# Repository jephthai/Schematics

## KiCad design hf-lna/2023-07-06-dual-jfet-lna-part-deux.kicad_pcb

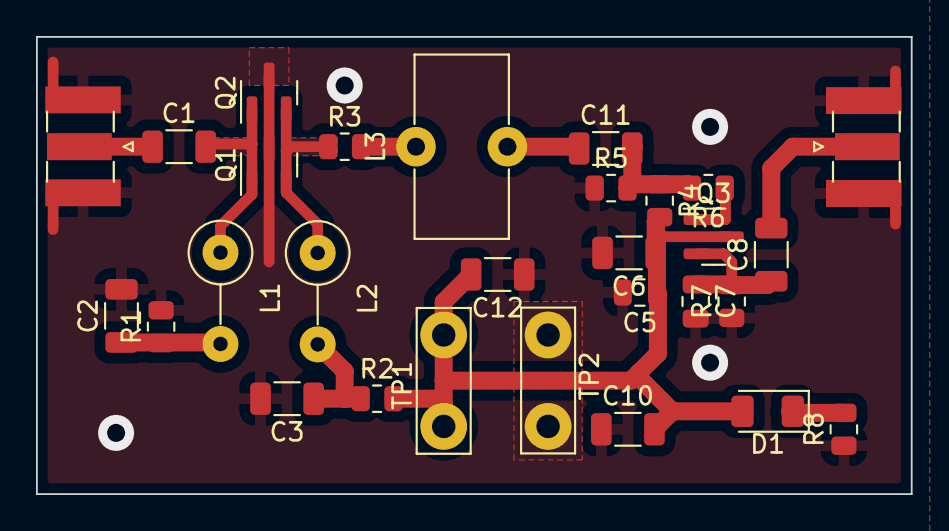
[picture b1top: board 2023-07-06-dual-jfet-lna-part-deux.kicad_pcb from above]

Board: 2 copper layers, 48.6 x 25.4 mm, 29 parts (0 on the bottom side), 14 nets.

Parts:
C1, C2, C3, C6, C8, C11, C12: 100n; C_1206_3216Metric
C5: 10n; C_0805_2012Metric
C7: 20p; C_0805_2012Metric
C10: 10u; C_1206_3216Metric
D1: LED; LED_1206_3216Metric
J1: RFIN; SMA-edge-mount
J2: RFOUT; SMA-edge-mount
L1, L2: 1m; L_Axial_L7.0mm_D3.3mm_P5.08mm_Vertical_Fastron_MICC
L3: 3u8; L_Toroid_Vertical_L10.0mm_W5.0mm_P5.08mm
Q1, Q2: MMBFJ310; SOT-23
Q3: MMBTH10; SOT-23
R1: 47; R_0805_2012Metric
R2: 330; R_0805_2012Metric
R3: 0; R_0805_2012Metric
R4, R5, R7: 1k; R_0805_2012Metric
R6: 10; R_0805_2012Metric
R8: 20k; R_0805_2012Metric
TP1: PWR+; TestPoint_Bridge_Pitch5.08mm_Drill1.3mm
TP2: PWR-; TestPoint_Bridge_Pitch5.08mm_Drill1.3mm

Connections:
+12V: C5.1, C6.1, C10.2, C12.2, D1.2 (A), Q3.3 (C), R2.2, R4.2, TP1.1
GND: C2.2, C3.2, C5.2, C6.2, C7.2, C10.1, C12.1, J1.2 (Ext), J2.2 (Ext), Q1.3 (G), Q2.3 (G), R1.2, R5.1, R7.1, R8.1, TP2.1
unnamed: C1.1, J1.1 (In)
unnamed: C1.2, L1.1, Q1.1 (D), Q2.1 (D)
unnamed: C2.1, L1.2, R1.1
unnamed: C3.1, L2.2, R2.1
unnamed: C7.1, C8.1, Q3.2 (E), R7.2
unnamed: C8.2, J2.1 (In)
unnamed: C11.1, L3.2
unnamed: C11.2, R4.1, R5.2, R6.2
unnamed: D1.1 (K), R8.2
unnamed: L2.1, Q1.2 (S), Q2.2 (S), R3.1
unnamed: L3.1, R3.2
unnamed: Q3.1 (B), R6.1

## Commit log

2023-07-12 HF LNA Experiment
